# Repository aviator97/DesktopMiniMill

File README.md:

DesktopMiniMill
===============

Plans, parts and configuration files for a desktop cnc machine. 
The DesktopMiniMill is controlled by LinuxCNC and Beaglebone Black. 
You can get a ready to go LinuxCNC from here: http://blog.machinekit.io/p/machinekit_16.html

This repository includes the CNC adapter PCB for the BBB and Pololu stepper drivers.

See the DMM in operation: http://youtu.be/r77spFATp_I

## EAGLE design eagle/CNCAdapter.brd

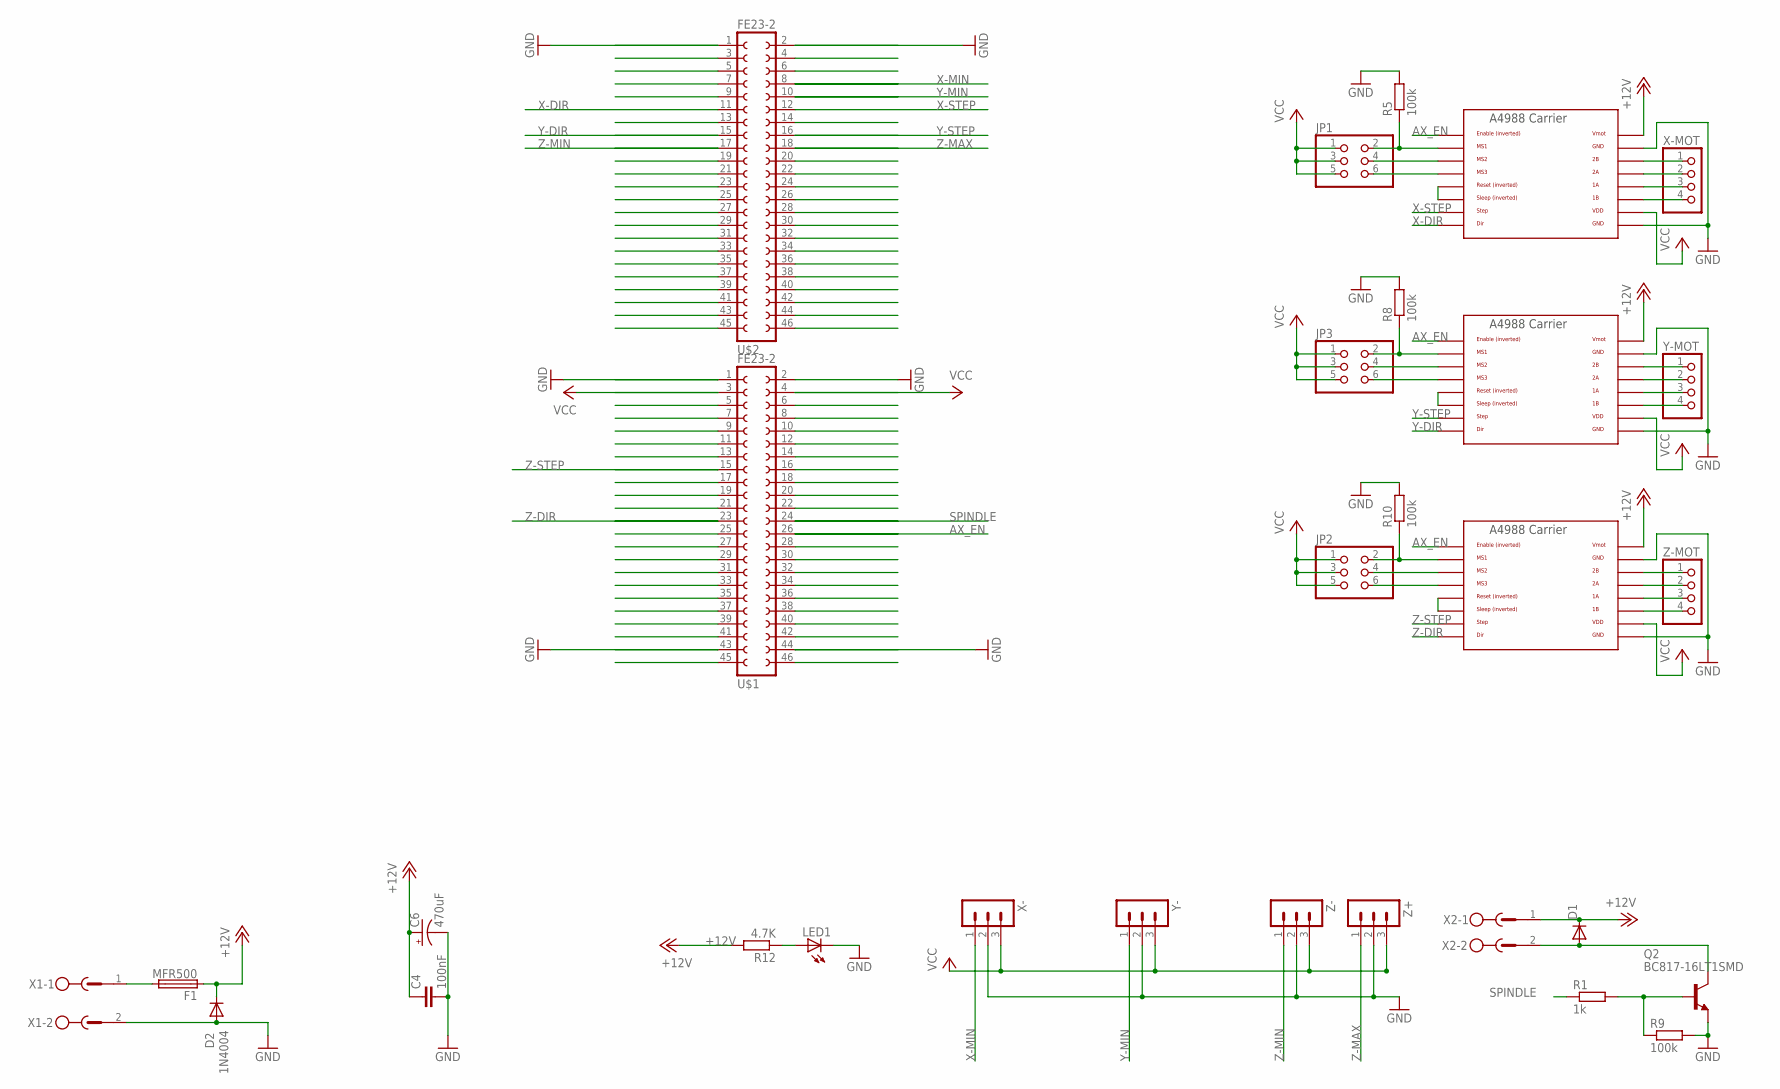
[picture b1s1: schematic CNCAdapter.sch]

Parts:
C4: 100nF; C2.5-3
C6: 470uF; E3,5-8
D1: DIODE-MINIMELF; MINIMELF
D2: 1N4004; DO41-10
F1: MFR500; LITTLEFUSE
JP1, JP2, JP3: PINHD-2X3; 2X03
LED1: LED3MM
Q2: BC817-16LT1SMD; SOT23-BEC
R1: 1k; R0805
R5, R8, R9, R10: 100k; R0805
R12: 4.7K; R0805
U$1, U$2: FE23-2
U$6, U$7, U$8: A4988BREAKOUT
X1, X2: MSTBV2
X-: 3PIN-HEADER
X-MOT: PINHD-1X4; 1X04
Y-: 3PIN-HEADER
Y-MOT: PINHD-1X4; 1X04
Z+: 3PIN-HEADER
Z-: 3PIN-HEADER
Z-MOT: PINHD-1X4; 1X04

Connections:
+12V: C4.1, C6.+, D1.C, D2.C, F1.1, R12.2, U$6.VMOT, U$7.VMOT, U$8.VMOT, X2.1
AX_EN: U$1.26, U$6.EN, U$7.EN, U$8.EN
GND: C4.2, C6.-, D2.A, LED1.K (C), Q2.E, R5.2, R8.2, R9.2, R10.2, U$1.1, U$1.2, U$1.43, U$1.44, U$2.1, U$2.2, U$6.GND, U$6.GND@0 (GND), U$7.GND, U$7.GND@0 (GND), U$8.GND, U$8.GND@0 (GND), X1.2, X-.2, Y-.2, Z+.2, Z-.2
unnamed: F1.2, X1.1
unnamed: D1.A, Q2.C, X2.2
unnamed: JP1.2, R5.1, U$6.MS1
unnamed: JP1.4, U$6.MS2
unnamed: JP3.4, U$7.MS2
unnamed: JP1.6, U$6.MS3
unnamed: U$6.RST, U$6.SLP (SLEEP)
unnamed: U$6.2B, X-MOT.1
unnamed: U$6.2A, X-MOT.2
unnamed: U$7.RST, U$7.SLP (SLEEP)
unnamed: U$6.1A, X-MOT.3
unnamed: U$6.1B, X-MOT.4
unnamed: U$7.2B, Y-MOT.1
unnamed: U$7.2A, Y-MOT.2
unnamed: U$7.1A, Y-MOT.3
unnamed: JP3.6, U$7.MS3
unnamed: JP3.2, R8.1, U$7.MS1
unnamed: U$7.1B, Y-MOT.4
unnamed: JP2.4, U$8.MS2
unnamed: U$8.RST, U$8.SLP (SLEEP)
unnamed: JP2.6, U$8.MS3
unnamed: JP2.2, R10.1, U$8.MS1
unnamed: U$8.2B, Z-MOT.1
unnamed: U$8.2A, Z-MOT.2
unnamed: U$8.1A, Z-MOT.3
unnamed: U$8.1B, Z-MOT.4
unnamed: LED1.A, R12.1
unnamed: Q2.B, R1.2, R9.1
SPINDLE: R1.1, U$1.24
VCC: JP1.1, JP1.3, JP1.5, JP2.1, JP2.3, JP2.5, JP3.1, JP3.3, JP3.5, U$1.3, U$1.4, U$6.VDD, U$7.VDD, U$8.VDD, X-.3, Y-.3, Z+.3, Z-.3
X-DIR: U$2.11, U$6.DIR
X-MIN: U$2.8, X-.1
X-STEP: U$2.12, U$6.STEP
Y-DIR: U$2.15, U$7.DIR
Y-MIN: U$2.10, Y-.1
Y-STEP: U$2.16, U$7.STEP
Z-DIR: U$1.23, U$8.DIR
Z-MAX: U$2.18, Z+.1
Z-MIN: U$2.17, Z-.1
Z-STEP: U$1.15, U$8.STEP

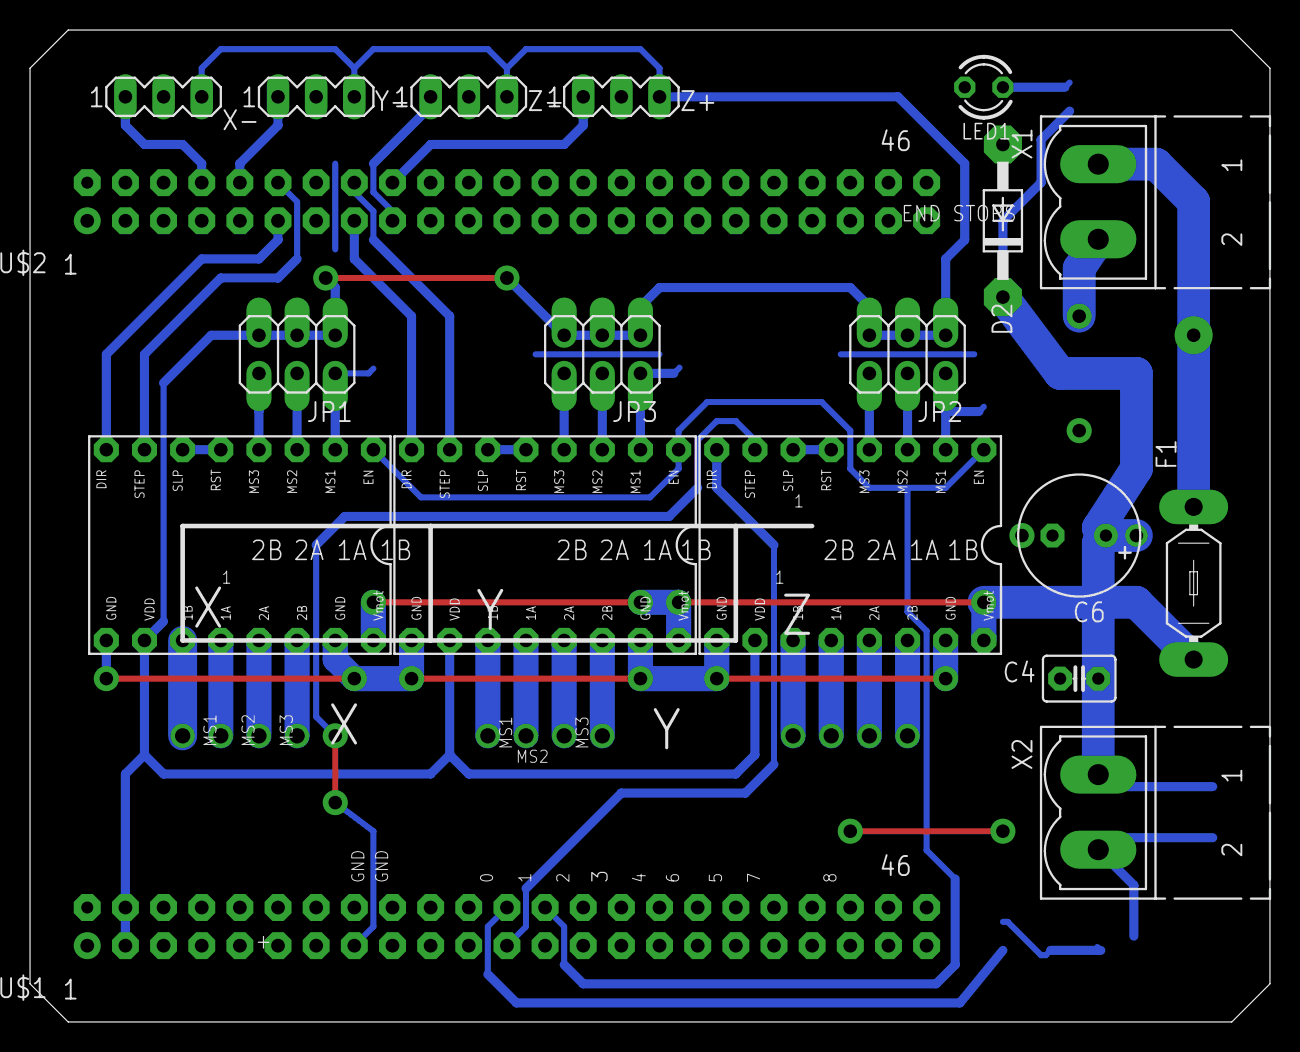
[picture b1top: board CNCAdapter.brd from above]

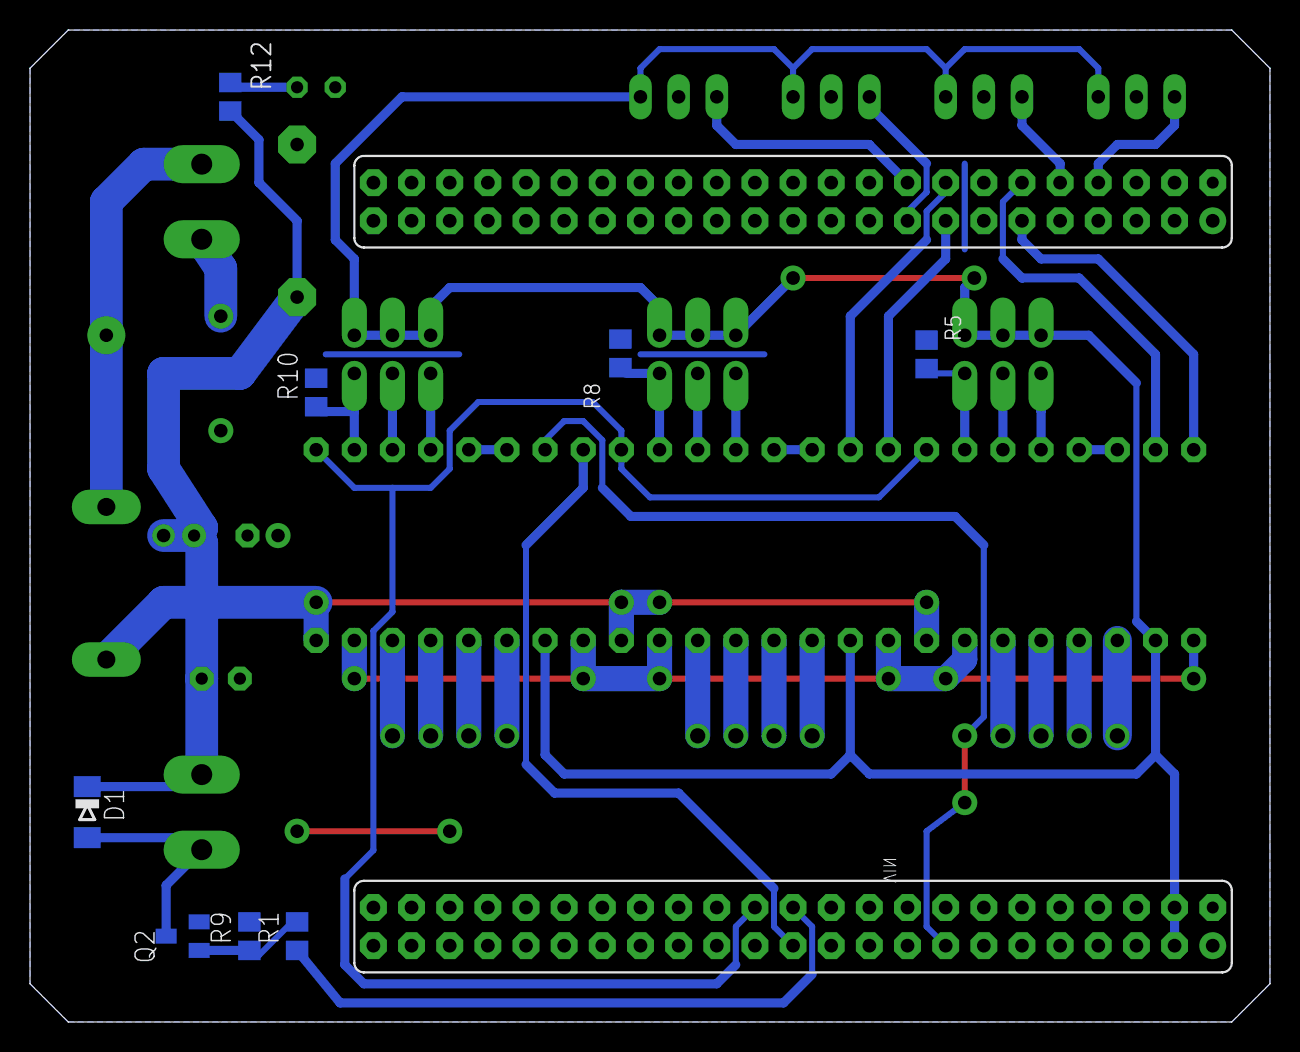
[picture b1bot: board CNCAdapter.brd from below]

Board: 2 copper layers, 82.5 x 66.0 mm, 30 parts (8 on the bottom side), 43 nets.

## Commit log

2014-02-21 first part
2014-02-21 Parts overview
2014-02-21 added lm8uu bearing holder
2014-02-22 added printed directory
2014-02-22 added some parts
2014-02-22 added picture
2014-02-22 added pcb
2014-02-22 added video
2014-02-22 typo
2014-02-23 added config files
2014-02-23 added Machinekit link
2014-02-23 added stl files
2014-02-26 added pic
2014-03-03 added design

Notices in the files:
eagle/CNCAdapter.brd:
GPL v3
eagle/CNCAdapter.sch:
Copyright 2014 Cord Johannmeyer
